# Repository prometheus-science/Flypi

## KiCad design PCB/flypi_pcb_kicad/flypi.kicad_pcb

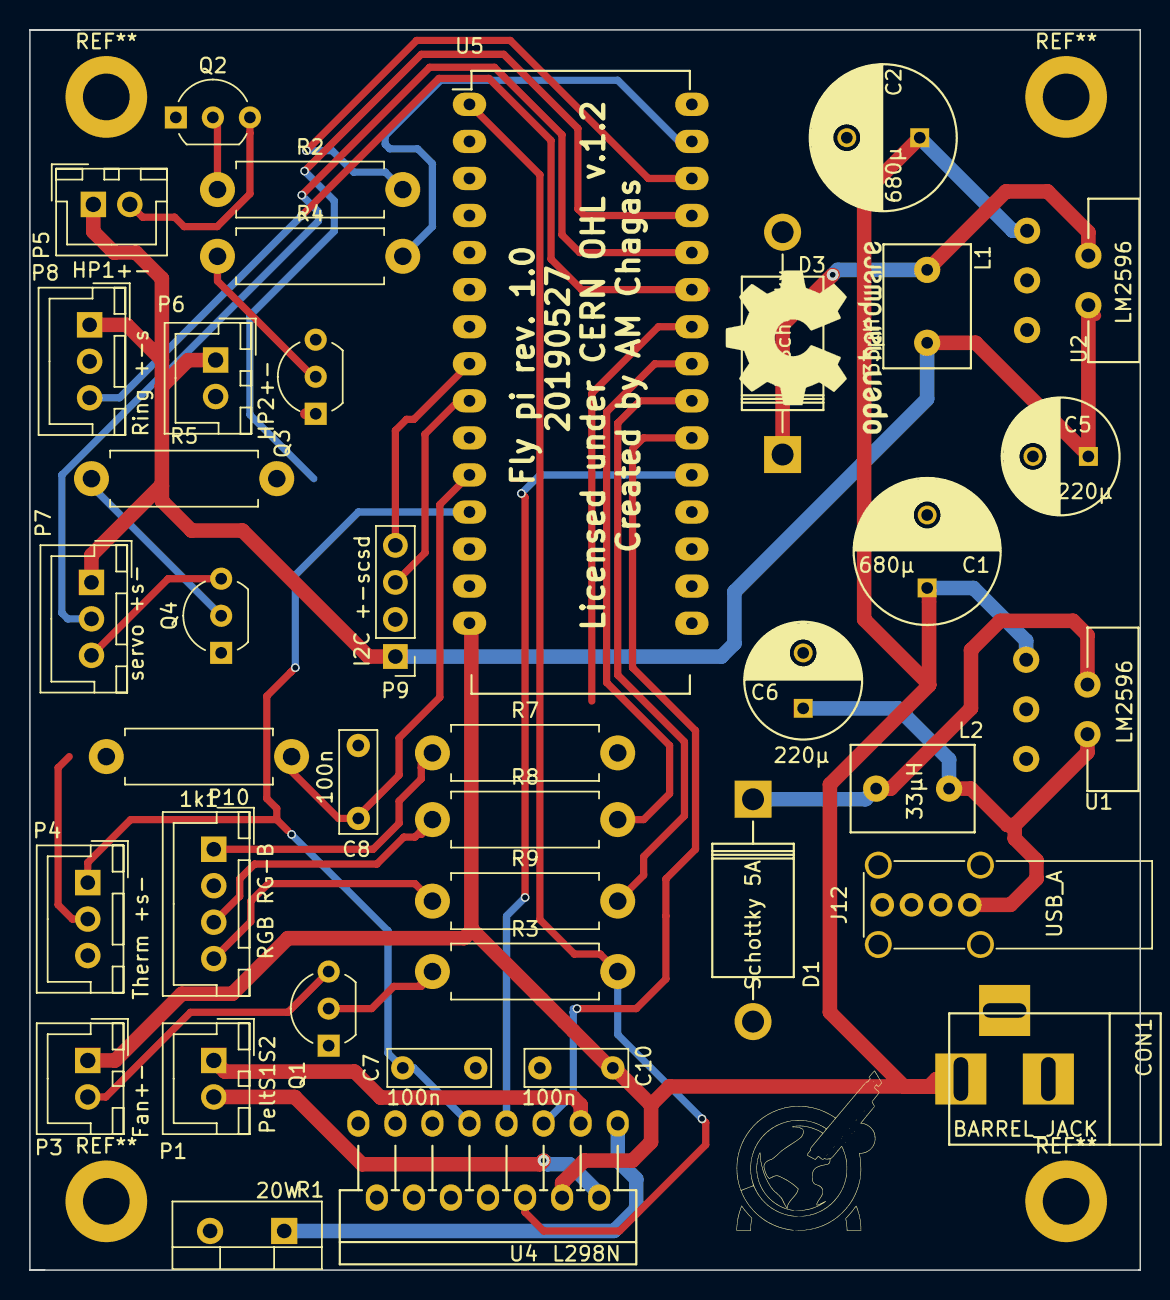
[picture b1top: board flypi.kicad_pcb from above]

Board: 2 copper layers, 76.1 x 85.0 mm, 39 parts (0 on the bottom side), 36 nets.

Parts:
1k1: R; R_Axial_DIN0411_L9.9mm_D3.6mm_P12.70mm_Horizontal
C1, C2: 680µ; C_Radial_D10_L21_P5
C5, C6: 220µ; C_Radial_D8_L13_P3.8
C7, C8, C10: 100n; C_Rect_L7.0mm_W2.5mm_P5.00mm
CON1: BARREL_JACK
D1: Schottky 5A; Diode_DO-201AD_Horizontal_RM15
D3: D_Schottky; Diode_DO-201AD_Horizontal_RM15
J12: USB_A; USB_A_Vertical
L1, L2: 33µH; Neosid_Inductor_MA-Bs75
P1: PeltS1S2; JST_XH_B02B-XH-A_02x2.50mm_Straight
P3: Fan+-; JST_XH_B02B-XH-A_02x2.50mm_Straight
P4: Therm +s-; JST_XH_B03B-XH-A_03x2.50mm_Straight
P5: HP1+-; JST_XH_B02B-XH-A_02x2.50mm_Straight
P6: HP2+-; JST_XH_B02B-XH-A_02x2.50mm_Straight
P7: servo +s-; JST_XH_B03B-XH-A_03x2.50mm_Straight
P8: Ring +-s; JST_XH_B03B-XH-A_03x2.50mm_Straight
P9: I2C +-scsd; Socket_Strip_Straight_1x04_Pitch2.54mm
P10: RGB RG-B; JST_XH_B04B-XH-A_04x2.50mm_Straight
Q1, Q3, Q4: 1A_NPN_EBC; TO-92_Inline_Wide
Q2: 1A-NPN-EBC; TO-92_Inline_Wide
R1: 20W; TO-220-2_Vertical
R2, R3, R4, R5, R7, R8, R9: 270; R_Axial_DIN0411_L9.9mm_D3.6mm_P12.70mm_Horizontal
U1, U2: LM2596
U4: L298N; Multiwatt_15_Vertical
U5: arduino_mini; DIP-30_W15.24mm_LongPads

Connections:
GND: C1.2, C2.2, C5.2, C6.2, C7.2, C8.1, C10.1, CON1.2, CON1.3, D1.2, D3.2, J12.4, J12.5, P4.3, P8.2, P9.2, P10.2, Q1.1, Q2.1, Q3.1, Q4.1, R1.2, U1.3, U1.5, U2.3, U2.5, U4.8, U5.14, U5.19
unnamed: 1k1.1, C8.2, U5.11
unnamed: 1k1.2, P4.2
unnamed: C1.1, C2.1, C10.2, CON1.1, P3.1, U1.1, U2.1, U4.4, U5.15
unnamed: C5.1, L1.2, P5.1, P6.1, P7.1, P8.1, P9.1, U2.4
unnamed: C6.1, J12.1, L2.2, U1.4
unnamed: C7.1, P4.1, U4.9, U5.12
unnamed: D1.1, L2.1, U1.2
unnamed: D3.1, L1.1, U2.2
unnamed: P1.1, U4.3
unnamed: P1.2, U4.2
unnamed: P3.2, Q1.3
unnamed: P5.2, Q2.3
unnamed: P6.2, Q3.3
unnamed: P7.2, U5.26
unnamed: P7.3, Q4.3
unnamed: P8.3, U5.25
unnamed: P9.3, U5.9
unnamed: P9.4, U5.8
unnamed: P10.1, R7.1
unnamed: P10.3, R8.1
unnamed: P10.4, R9.1
unnamed: Q1.2, R3.1
unnamed: Q2.2, R2.1
unnamed: Q3.2, R4.1
unnamed: Q4.2, R5.1
unnamed: R1.1, U4.1
unnamed: R2.2, U5.28
unnamed: R3.2, U4.6, U5.1
unnamed: R4.2, U5.29
unnamed: R5.2, U5.27
unnamed: R7.2, U5.24
unnamed: R8.2, U5.23
unnamed: R9.2, U5.22
unnamed: U4.5, U5.21
unnamed: U4.7, U5.20

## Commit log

2018-04-19 changed license and new folder
    we are practising with github desktop and I made changes to learn a bit, they don't actually mean anything.
2019-05-27 added light diffuser step and stl
2019-05-27 update PCB, change resistor values: 220 for 270, change resistor footprints (shorter footprint), re-wire npn transistors -> now (-) side is being switched on/off, add some logos, change board license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
2019-06-13 reorganize 3D print files
2019-07-01 added servo gears
2019-07-04 update base

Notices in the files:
PCB/flypi_pcb_kicad/flypi.kicad_pcb:
Licensed under CERN OHL v.1.2
